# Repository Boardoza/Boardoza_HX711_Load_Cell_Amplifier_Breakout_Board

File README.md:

# Boardoza HX711 24-Bit ADC Module

The HX711 24-Bit Analog-to-Digital Converter (ADC) Module is designed for precision load cell measurements, making it ideal for electronic weighing scales and industrial control applications. It features a low-noise programmable gain amplifier and supports two selectable differential input channels. The module operates with low power consumption, making it suitable for battery-powered applications.

## [Click here to purchase!](https://ozdisan.com/maker-ve-iot-urunleri/boardoza/boardoza-modulleri/BOARDOZA-HX711/1206514)

|Front Side|Back Side|
|:---:|:---:|
| | |

---

## Key Features

- 24-bit ADC designed for weigh scales and industrial applications.
- Two selectable differential input channels (To use channel B, R7(100R), R8(100R), and C8(100nF) must be populated).
- Low power consumption: <1.5mA in normal operation, <1µA in power-down mode.
- Integrated low-noise programmable gain amplifier.
- Selectable output data rates: 10SPS or 80SPS.
- Wide operating voltage range: 2.7V to 5.5V.

---

## Technical Specifications

**Input Voltage:** 2.7V - 5.5V  
**Functions:** 24-Bit ADC for load cells and weigh scales  
**Supply Current:** 1.5mA  
**Operating Temperature:** -40°C ~ +85°C  
**Board Dimensions:** 20mm x 40mm  

---

## Board Pinout

### J1 Connector

| Pin Number | Pin Name | Description |
| :---: | :---: | --- |
| 1 | VCC | 2.7V - 5.5V Power Input |
| 2 | VDD | 2.7V - 5.5V Power Input |
| 3 | DAT | Serial Data Output |
| 4 | CLK | Serial Clock Input |
| 5 | GND | Ground |

### J2 Connector

| Pin Number | Pin Name | Description |
| :---: | :---: | --- |
| 1 | B+ | Positive Signal (Second Channel) |
| 2 | B- | Negative Signal (Second Channel) |

### J3 Connector (Load Cell Interface)

| Pin Number | Pin Name | Description |
| :---: | :---: | --- |
| 1 | RED/E+ | + Excitation |
| 2 | BLK/E- | - Excitation |
| 3 | WHT/A- | - Signal |
| 4 | GRN/A+ | + Signal |

### JP1 Jumper Settings

| Pin Configuration | Data Rate |
| :---: | --- |
| 1-2 | 80 Samples per Second (SPS) |
| 2-3 | 10 Samples per Second (SPS) |

---

## Board Dimensions

---

## Step Files

[Boardoza HX711.step](./assets/HX711%20Step.step)

---

## Datasheet

[Boardoza HX711 Datasheet.pdf](./assets/HX711%20Datasheet.pdf)

---

## Version History

- V1.0.0 - Initial Release

---

## Support

- If you have any questions or need support, please contact <support@boardoza.com>

---

## License

Shield: [![CC BY-SA 4.0][cc-by-sa-shield]][cc-by-sa]

This work is licensed under a [Creative Commons Attribution-ShareAlike 4.0 International License][cc-by-sa].

[![CC BY-SA 4.0][cc-by-sa-image]][cc-by-sa]

[cc-by-sa]: http://creativecommons.org/licenses/by-sa/4.0/
[cc-by-sa-image]: https://licensebuttons.net/l/by-sa/4.0/88x31.png
[cc-by-sa-shield]: https://img.shields.io/badge/License-CC%20BY--SA%204.0-lightgrey.svg

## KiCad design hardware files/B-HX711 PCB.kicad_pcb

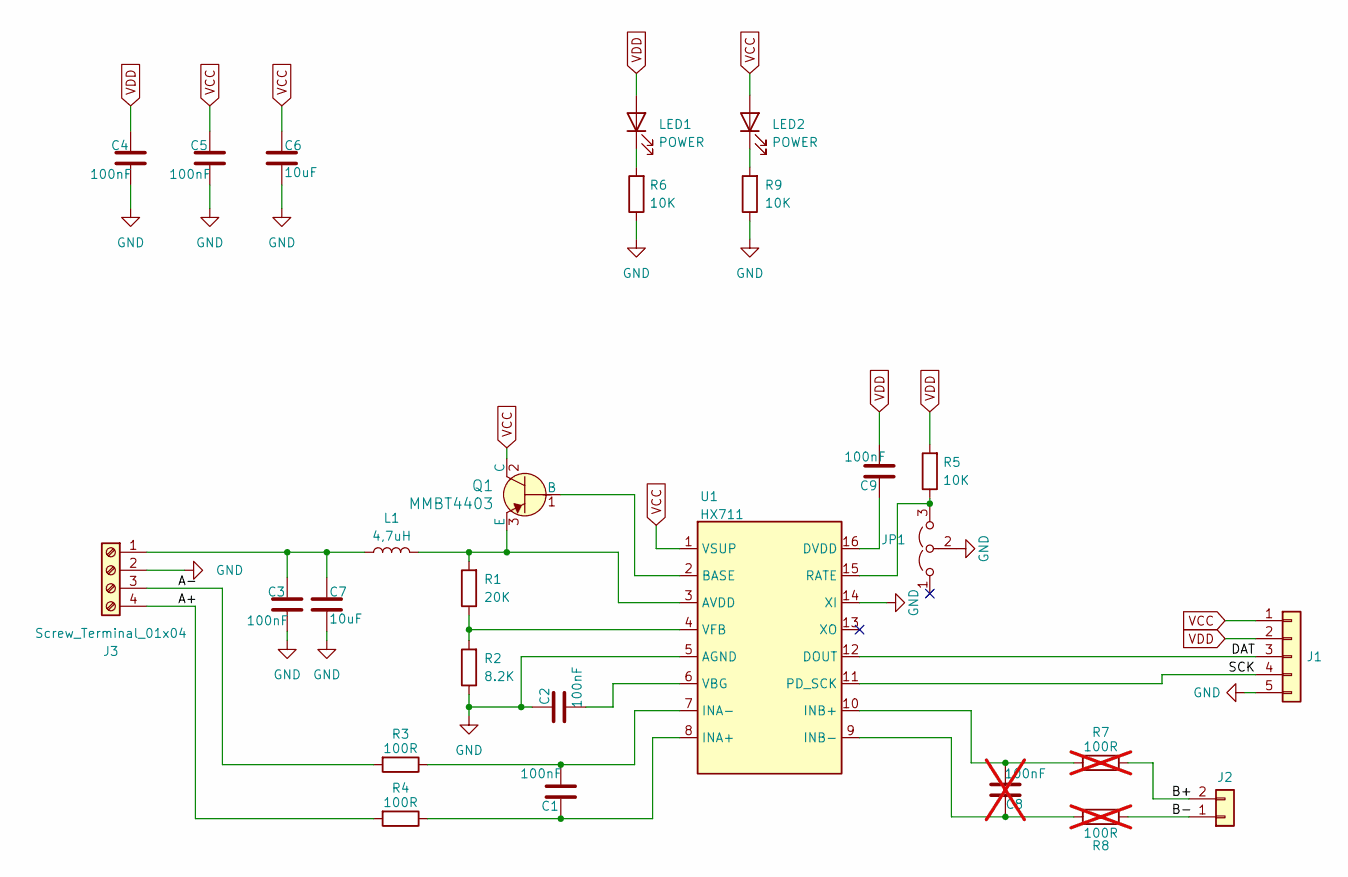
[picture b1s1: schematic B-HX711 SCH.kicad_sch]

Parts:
C1, C2, C3, C4, C5, C9: 100nF; C_0603_1608Metric; MPN CL10B104KB8NNNC
C6, C7: 10uF; C_1210_3225Metric; MPN CL10A106KQ8NNNC
C8: 100nF; C_0603_1608Metric; not fitted
J1: Conn_01x05; 2317-05S_1x05_P2.50mm_Vertical
J2: Conn_01x02; 2317-02S_1x02_P2.50mm_Vertical; MPN DG350-3.5-02P-14-00AH
J3: Screw_Terminal_01x04; TerminalBlock_MetzConnect_Type059_RT06304HBWC_1x04_P3.50mm_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; MPN DG350-3.5-02P-14-00AH
JP1: Jumper_3_Open; PinHeader_1x03_P2.54mm_Vertical; MPN L-KLS1-207-1-03-S
L1: 4,7uH; L_0805_2012Metric
LED1, LED2: POWER; LED_0603_1608Metric; MPN 19-213USRC/S259/TR8
Q1: MMBT4403; SOT-23-3; MPN MMBT4403_R1_00001
R1: 20K; R_0603_1608Metric; MPN 0603SAJ0203T5E
R2: 8.2K; R_0603_1608Metric; MPN 0603SAJ0822T5E
R3, R4: 100R; R_0603_1608Metric; MPN CQ03SAJ0101T5E
R5, R6, R9: 10K; R_0603_1608Metric; MPN 0603SAJ0103T5E
R7, R8: 100R; R_0603_1608Metric; not fitted
U1: HX711; SOP-16_3.9x9.9mm_P1.27mm; MPN HX711

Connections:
/A+: J3.4, R4.2
/A-: J3.3, R3.2
/B+: J2.2, R7.1
/B-: J2.1, R8.1
/DAT: J1.3, U1.12 (DOUT)
/SCK: J1.4, U1.11 (PD_SCK)
GND: C2.1, C3.1, C4.1, C5.1, C6.2, C7.2, J1.5, J3.2, JP1.2 (C), R2.1, R6.1, R9.1, U1.5 (AGND), U1.14 (XI)
unnamed: C3.2, C7.1, J3.1, L1.1
unnamed: JP1.3 (B), R5.1, U1.15 (RATE)
unnamed: LED1.1 (K), R6.2
unnamed: LED2.1 (K), R9.2
unnamed: Q1.1 (B), U1.2 (BASE)
unnamed: L1.2, Q1.3 (E), R1.2, U1.3 (AVDD)
unnamed: C9.1, U1.16 (DVDD)
unnamed: C1.1, R4.1, U1.8 (INA+)
unnamed: C1.2, R3.1, U1.7 (INA-)
unnamed: C8.2, R7.2, U1.10 (INB+)
unnamed: C8.1, R8.2, U1.9 (INB-)
unnamed: C2.2, U1.6 (VBG)
unnamed: R1.1, R2.2, U1.4 (VFB)
VCC: C5.2, C6.1, J1.1, LED2.2 (A), Q1.2 (C), U1.1 (VSUP)
VDD: C4.2, C9.2, J1.2, LED1.2 (A), R5.2

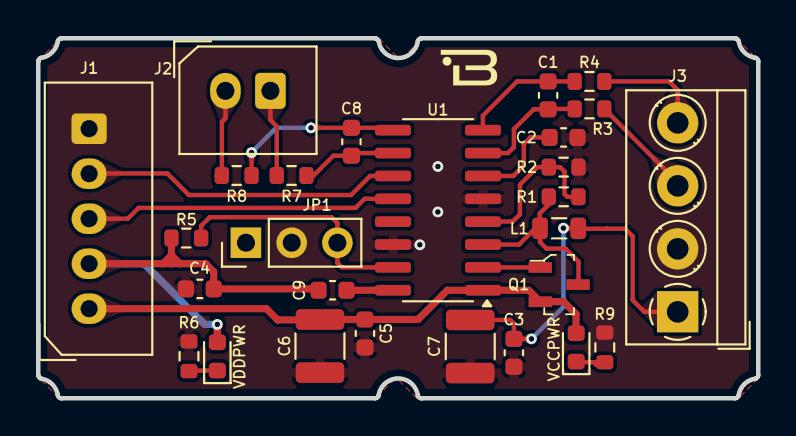
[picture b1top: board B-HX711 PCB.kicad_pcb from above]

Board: 2 copper layers, 40.0 x 20.0 mm, 27 parts (0 on the bottom side), 22 nets.

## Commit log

2024-09-05 Initial release of HX711 breakout board.
2025-03-17 Update README.md to enhance module description, design files and key features
2025-03-24 Add HX711 library
